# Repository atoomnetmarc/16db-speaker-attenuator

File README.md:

A simple resistive divider network to dampen the output of an audio amplifier 16db.

## The problem

See that spike at 6kHz? It was always there no matter what volume my Logitech Z-5500 Digital was set to. Very annoying.

The solution was this attenuator circuit that was fitted to each of the 5 channels of the amplifier. That peak at 6kHz is now 16db less annoying. Problem solved.

## Front

## Back

With instructions on how to tune the final resistor values.

## 1/2 3d printable enclosure

Print 2, they fit together. There are slots in which the pcb's fit.

## The result

With 2 years of collected dust, but hey, it works :-)

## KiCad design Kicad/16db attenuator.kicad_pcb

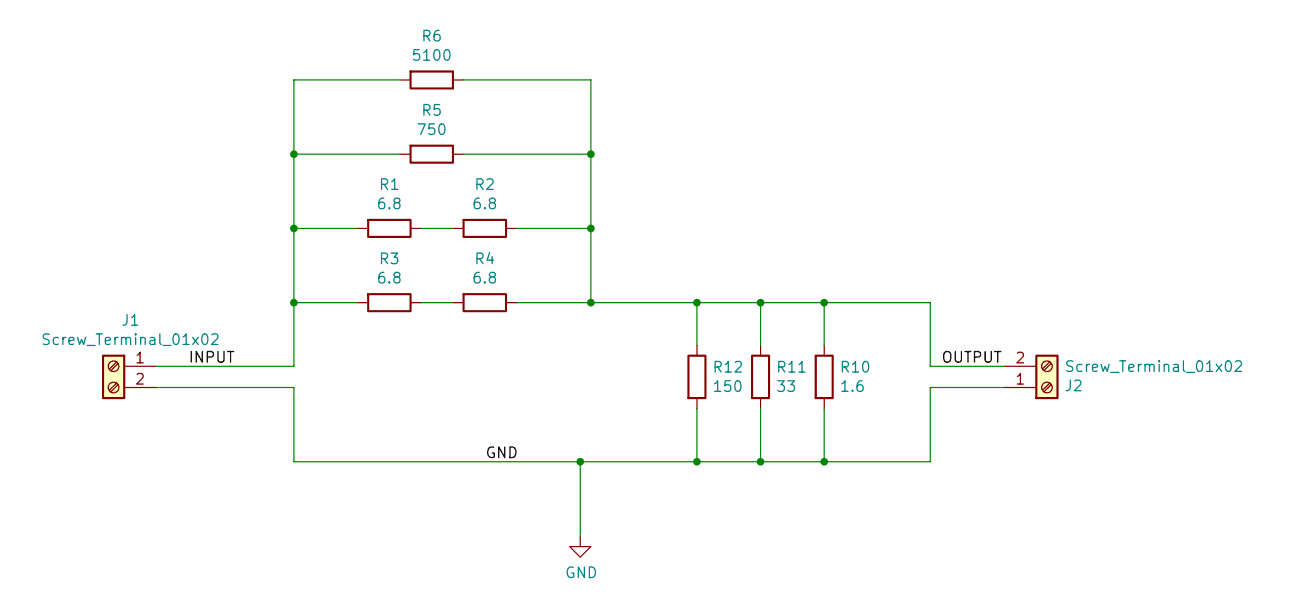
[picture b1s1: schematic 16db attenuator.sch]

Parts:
J1, J2: Screw_Terminal_01x02; TerminalBlock_Altech_AK300-2_P5.00mm
R1, R2, R3, R4: 6.8; R_Axial_DIN0918_L18.0mm_D9.0mm_P25.40mm_Horizontal
R5: 750; R_Axial_DIN0207_L6.3mm_D2.5mm_P10.16mm_Horizontal
R6: 5100; R_Axial_DIN0207_L6.3mm_D2.5mm_P10.16mm_Horizontal
R10: 1.6; R_Axial_DIN0918_L18.0mm_D9.0mm_P25.40mm_Horizontal
R11: 33; R_Axial_DIN0207_L6.3mm_D2.5mm_P10.16mm_Horizontal
R12: 150; R_Axial_DIN0207_L6.3mm_D2.5mm_P10.16mm_Horizontal

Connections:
/INPUT: J1.1, R1.2, R3.2, R5.2, R6.2
/OUTPUT: J2.2, R2.1, R4.1, R5.1, R6.1, R10.1, R11.1, R12.1
GND: J1.2, J2.1, R10.2, R11.2, R12.2
unnamed: R1.1, R2.2
unnamed: R3.1, R4.2

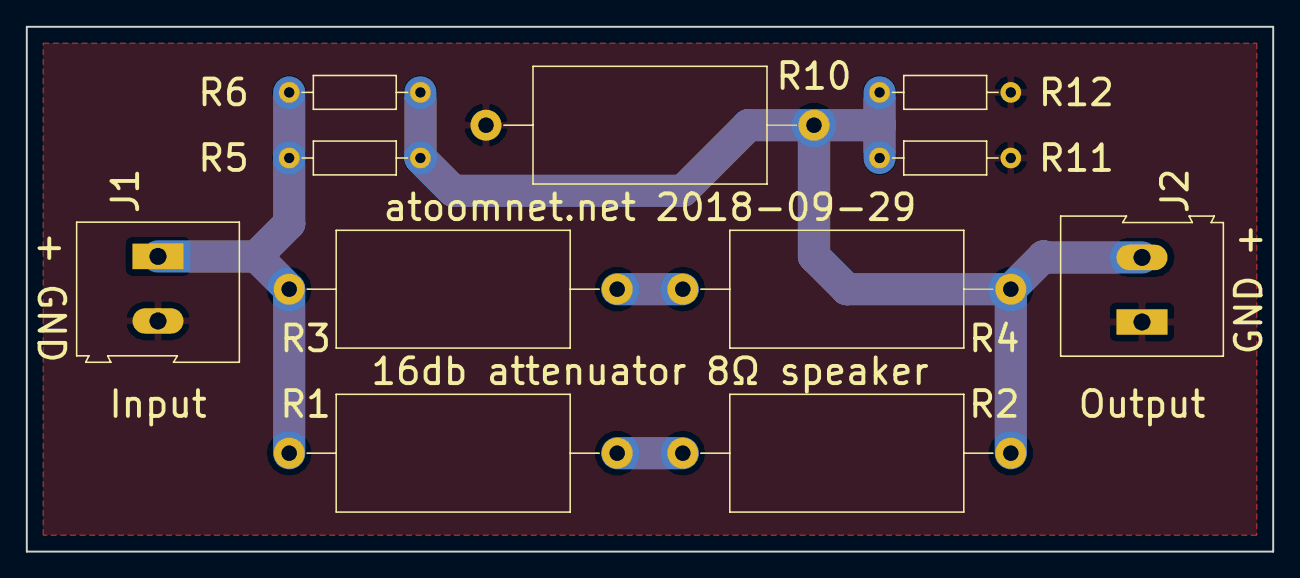
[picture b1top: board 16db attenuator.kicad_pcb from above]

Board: 2 copper layers, 96.5 x 40.6 mm, 11 parts (0 on the bottom side), 5 nets.

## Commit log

2025-11-01 Fix typo.
2026-01-23 Add CONTRIBUTING.md

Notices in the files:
README.md:
License: Apache 2.0
